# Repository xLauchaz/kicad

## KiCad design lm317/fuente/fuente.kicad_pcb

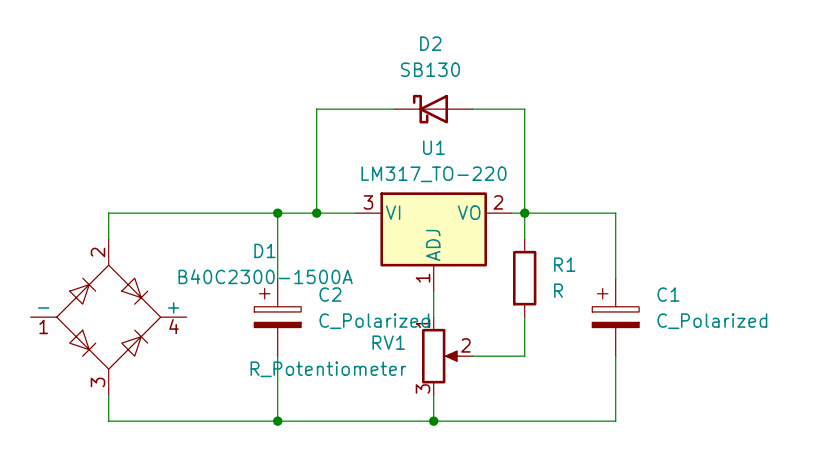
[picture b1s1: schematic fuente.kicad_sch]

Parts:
C1, C2: C_Polarized; CP_Radial_D5.0mm_P2.50mm
D1: B40C2300-1500A; Diode_Bridge_19.0x3.5x10.0mm_P5.0mm
D2: SB130; D_DO-41_SOD81_P10.16mm_Horizontal
R1: R; R_Axial_DIN0204_L3.6mm_D1.6mm_P5.08mm_Horizontal
RV1: R_Potentiometer; Potentiometer_Piher_T-16H_Single_Horizontal
U1: LM317_TO-220; TO-220-3_Vertical

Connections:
unnamed: C1.2, C2.2, D1.3, RV1.3
unnamed: C1.1, D2.2 (A), R1.1, U1.2 (VO)
unnamed: C2.1, D1.2, D2.1 (K), U1.3 (VI)
unnamed: R1.2, RV1.2
unnamed: RV1.1, U1.1 (ADJ)

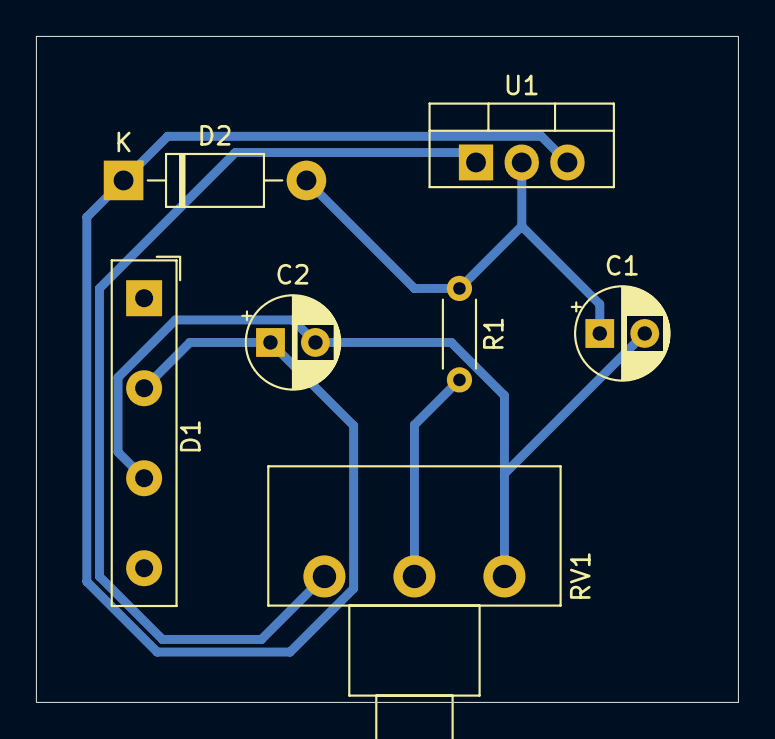
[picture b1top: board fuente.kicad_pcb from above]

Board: 2 copper layers, 39.0 x 37.0 mm, 7 parts (0 on the bottom side), 5 nets.

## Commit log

2025-04-28 Comit proyectos
2025-04-28 verificando
2025-05-09 cicuito
